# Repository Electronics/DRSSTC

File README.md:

# DRSSTC
Dual Resonant Solid State Tesla Coil Design Documentation and Code

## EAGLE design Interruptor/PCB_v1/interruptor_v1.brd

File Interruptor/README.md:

# Polyphonic Interruptor

Designed as a driver for DRSSTC's, with extra features such as MIDI input, a zero-crossing detector and frequency generator.

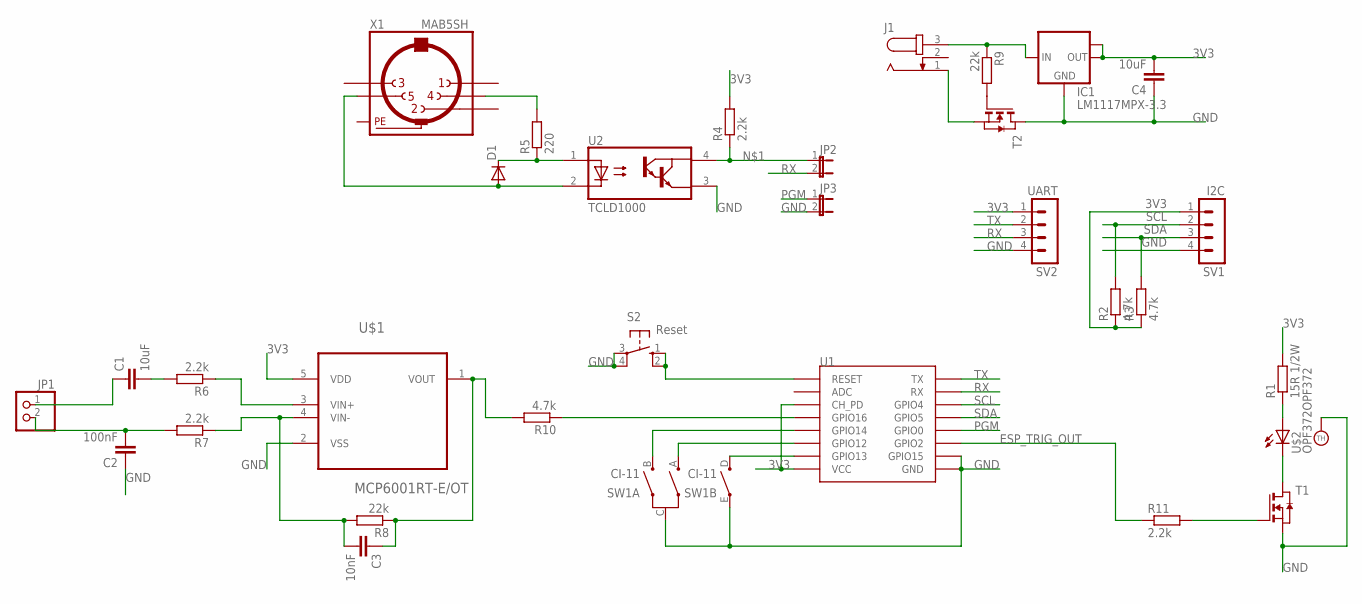
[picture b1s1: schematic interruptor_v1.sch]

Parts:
C1, C4: 10uF; C0805
C2: 100nF; C0805
C3: 10nF; C0805
D1: DIODE-DO214AA; DO214AA
IC1: LM1117MPX-3.3; SOT223
J1: JACK-PLUG0; SPC4077
JP1: PINHD-1X2; 1X02
JP2, JP3: JP1E; JP1
R1: 15R 1/2W; M0805
R2, R3, R10: 4.7k; M0805
R4, R6, R7, R11: 2.2k; M0805
R5: 220; M0805
R8, R9: 22k; M0805
S2: Reset; B3F-10XX
SV1: I2C; MA04-1
SV2: UART; MA04-1
SW1: CI-11
T1, T2: NMOSSOT23; SOT-23
U1: ESP12SMD; ESP12-SMD
U2: TCLD1000; SOIC254P1020X230-4N
U$1: MCP6001RT-E/OT; SOT95P270X145-5N
U$2: OPF372OPF372; OPF372
X1: MAB5SH

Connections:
3V3: C4.2, IC1.2 (OUT), IC1.TAB (OUT1), R1.2, R2.1, R3.1, R4.2, SV1.1, SV2.1, U1.CH_PD, U1.VCC, U$1.5 (VDD)
ESP_TRIG_OUT: R11.1, U1.GPIO2
GND: C2.1, C4.1, IC1.1 (GND), JP3.2, S2.3, S2.4 (P1), SV1.4, SV2.4, SW1.C, SW1.E, T1.2 (S), T2.1 (D), U1.GND, U1.GPIO15, U2.3 (E1), U$1.2 (VSS), U$2.CASE (TH)
unnamed: JP2.1, R4.1, U2.4 (CO1)
unnamed: R5.2, X1.4
unnamed: D1.C, R5.1, U2.1 (A1)
unnamed: D1.A, U2.2 (C1), X1.5
unnamed: SW1.D, U1.GPIO13
unnamed: C1.1, JP1.1
unnamed: C2.2, JP1.2, R7.2
unnamed: C1.2, R6.2
unnamed: R6.1, U$1.3 (VIN+)
unnamed: C3.2, R7.1, R8.2, U$1.4 (VIN-)
unnamed: SW1.A, U1.GPIO12
unnamed: C3.1, R8.1, R10.2, U$1.1 (VOUT)
unnamed: SW1.B, U1.GPIO14
unnamed: T1.1 (D), U$2.CATHODE (C)
unnamed: S2.1 (S), S2.2 (S1), U1.RESET
unnamed: R1.1, U$2.ANODE (A)
unnamed: J1.1, T2.2 (S)
unnamed: IC1.3 (IN), J1.3, R9.1
unnamed: R9.2, T2.3 (G)
unnamed: R10.1, U1.GPIO16
unnamed: R11.2, T1.3 (G)
PE: X1.PE, X1.PE@ (PE)
PGM: JP3.1, U1.GPIO0
RX: JP2.2, SV2.3, U1.RXD0 (RX)
SCL: R2.2, SV1.2, U1.GPIO4
SDA: R3.2, SV1.3, U1.GPIO5
TX: SV2.2, U1.TXD0 (TX)

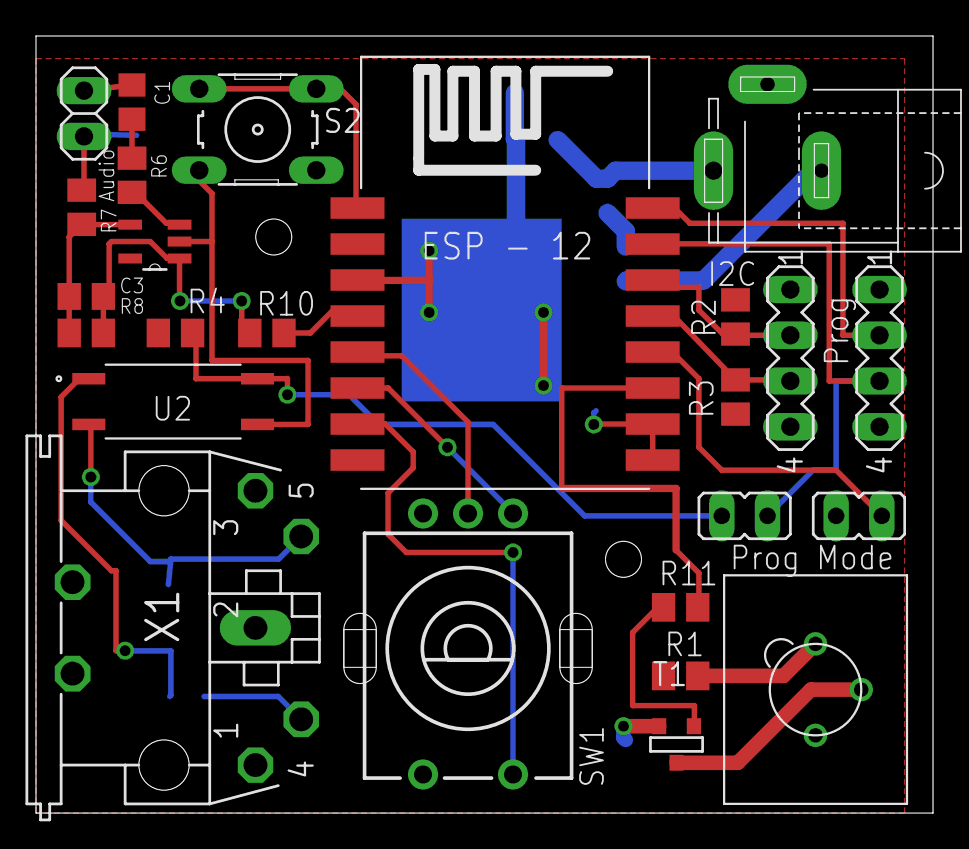
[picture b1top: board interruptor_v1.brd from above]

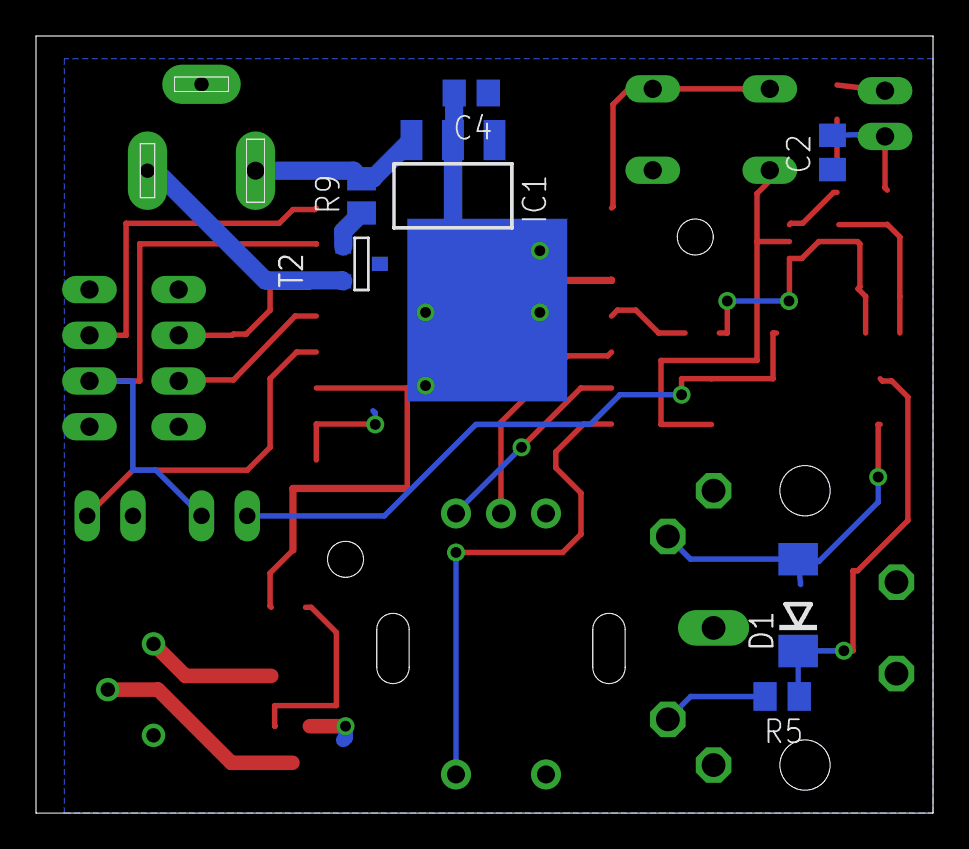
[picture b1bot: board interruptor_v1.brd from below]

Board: 2 copper layers, 49.8 x 43.2 mm, 32 parts (7 on the bottom side), 30 nets.

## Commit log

2018-05-20 Working interrupter code for Uno and ESP8266-12
2018-05-20 Update License
2018-05-21 Move files around, add files for PCB design.
2018-05-22 Schematic of ZCD and MIDI
2018-05-22 Finished with 1/4
2018-05-22 No DRC, now to route
2018-05-22 No DRC errors other than drill sizes, routed
2018-05-22 Fixed small alignment error and board edge
2018-05-23 placed tname/bname silkscreen
2018-05-23 Fixed dimension error
